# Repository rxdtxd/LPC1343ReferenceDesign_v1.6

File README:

This is a version of microBuilder.eu LPC1343 Reference Board [1],
slightly modified:

- the ocillator footprint is replaced with a HC49/S, these crystals
  are available locally and cheaper;
- spacings are slightly increased (manufacturer requirements);
- silkscreen is now retarded.

[1]: http://www.microbuilder.eu/Projects/LPC1343ReferenceDesign.aspx

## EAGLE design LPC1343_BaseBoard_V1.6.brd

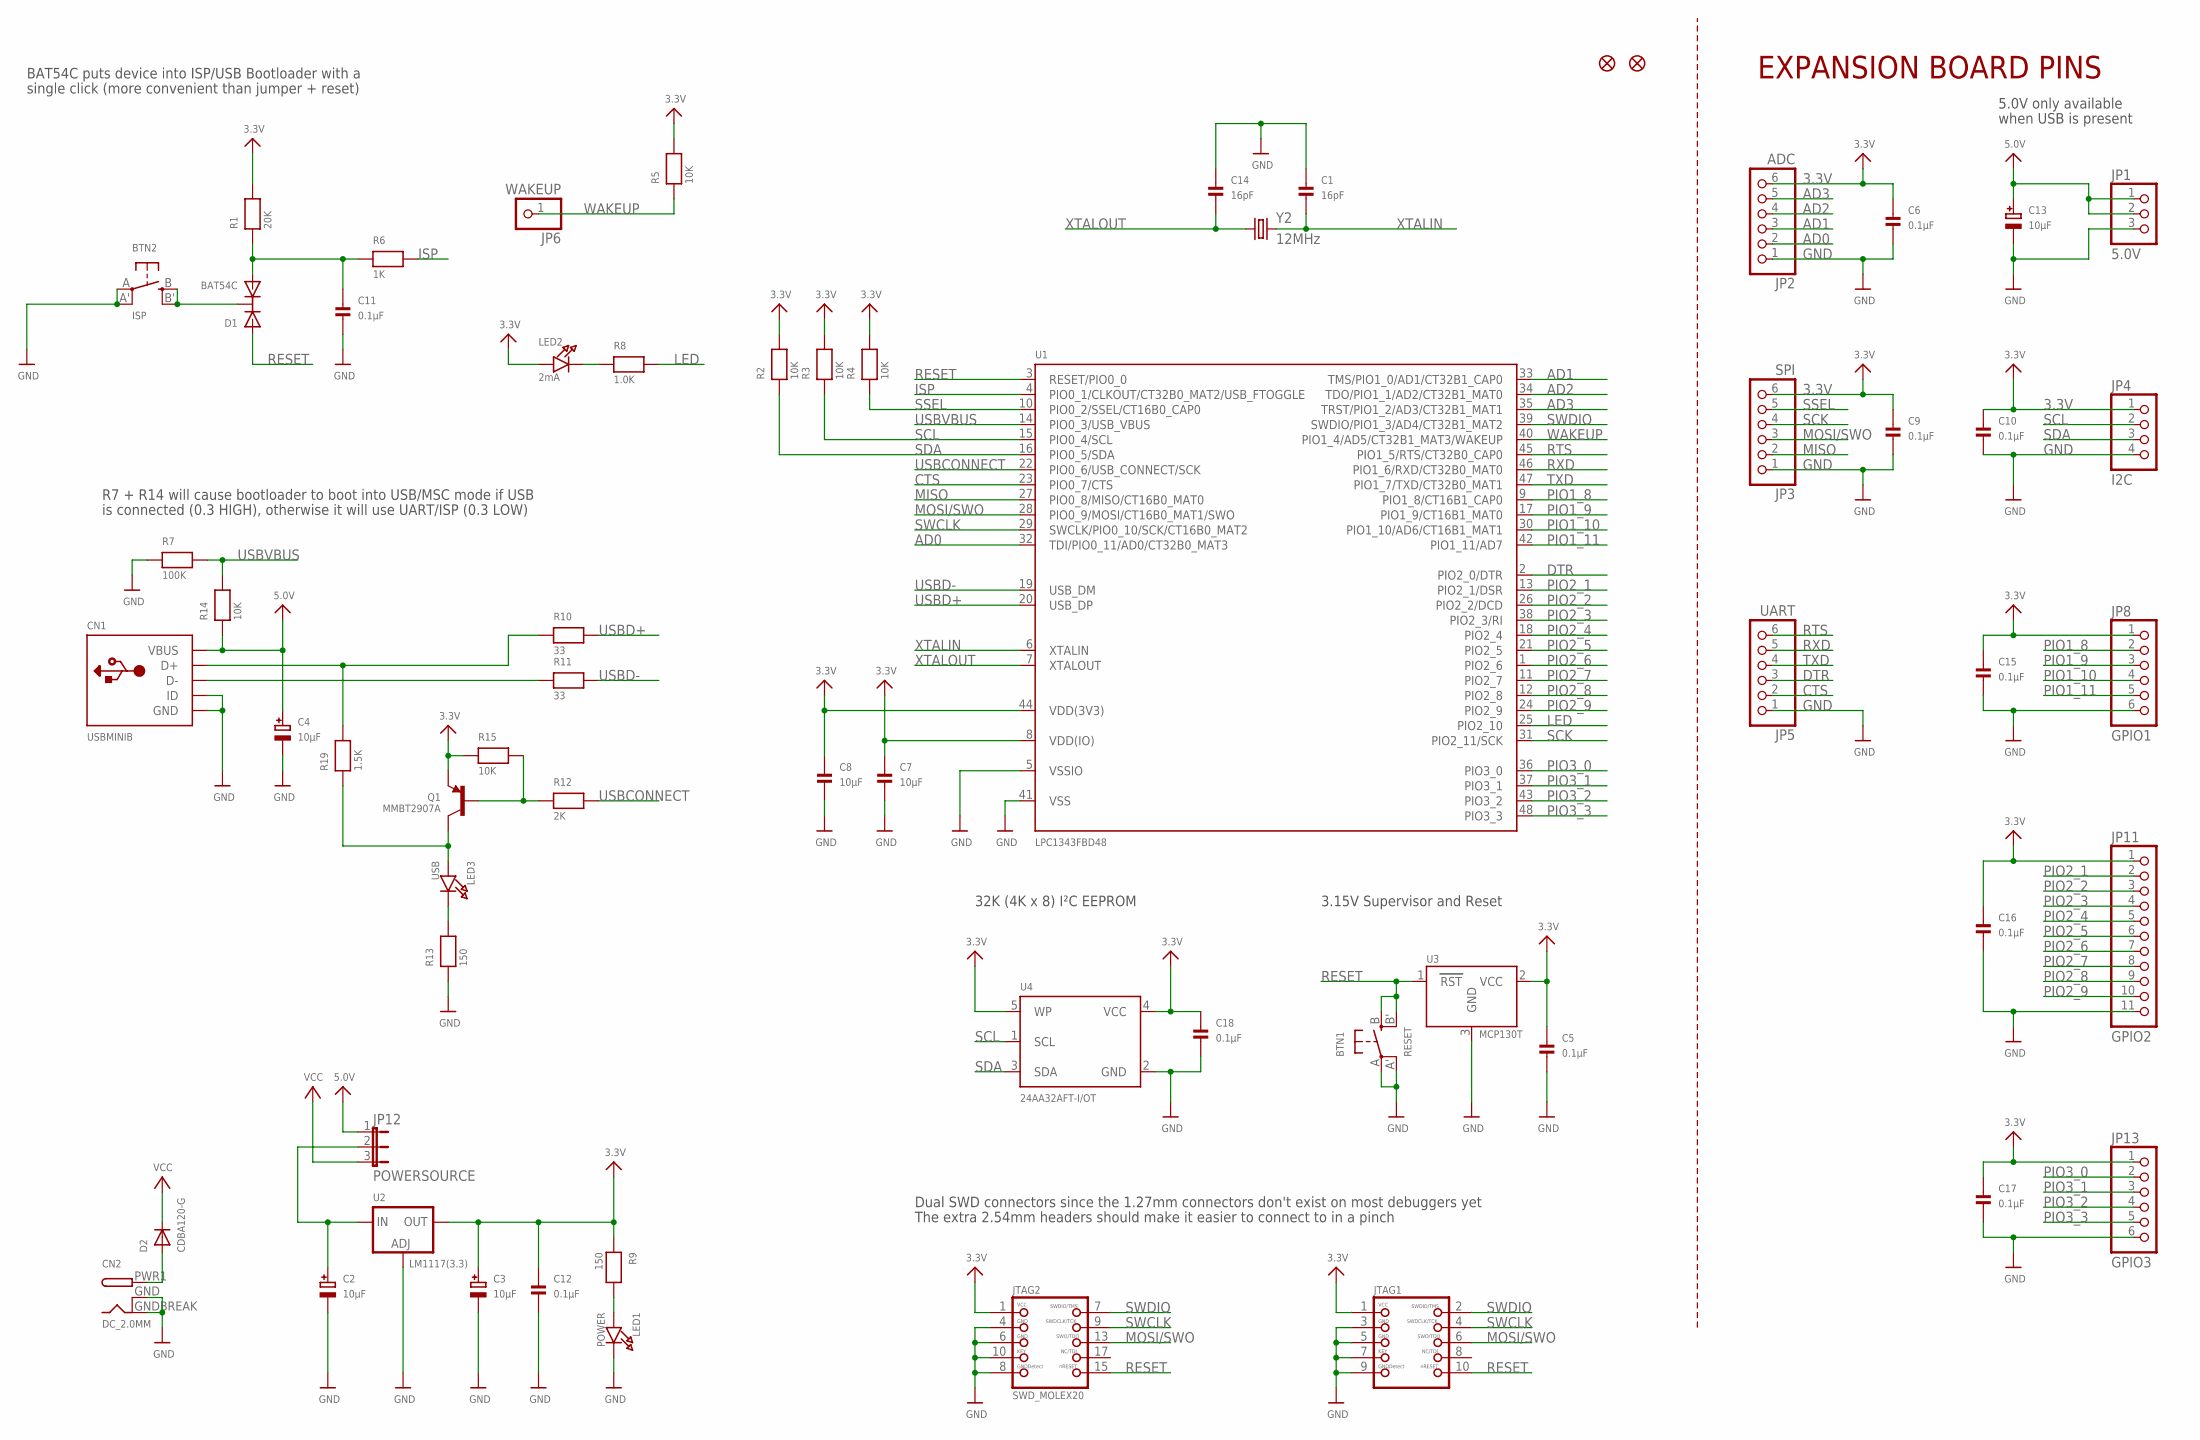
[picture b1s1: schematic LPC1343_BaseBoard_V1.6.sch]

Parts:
BTN1: RESET; EVQ-Q2
BTN2: ISP; EVQ-Q2
C1, C14: 16pF; 0603
C2, C3, C4, C13: 10µF; EIA3216-18/A-R
C5, C6, C9, C10, C11, C12, C15, C16, C17, C18: 0.1µF; 0603
C7, C8: 10µF; 0805
CN1: USBMINIB; USB-MINIB
CN2: DC_2.0MM; DCJACK_2MM_SMT
D1: BAT54C; SOT23-R
D2: CDBA120-G; SMADIODE
JP1: 5.0V; 1X03_ROUND
JP2: ADC; 1X06_ROUND
JP3: SPI; 1X06_ROUND
JP4: I2C; 1X04_ROUND
JP5: UART; 1X06_ROUND
JP6: WAKEUP; 1X01_ROUND
JP7, JP9: FIDUCIAL1X2.5; FIDUCIAL-1X2.5
JP8: GPIO1; 1X06_ROUND
JP11: GPIO2; 1X11_ROUND
JP12: POWERSOURCE; JUMPER3
JP13: GPIO3; 1X06_ROUND
JTAG1: JTAG-CORTEXM3; 2X05_1.27MM_SMT
JTAG2: SWD_MOLEX20; JTAG-ARM
LED1: POWER; CHIPLED_0805
LED2: 2mA; CHIPLED_0805
LED3: USB; CHIPLED_0805
Q1: MMBT2907A; SOT23-R
R1: 20K; 0603
R2, R3, R4, R5, R14, R15: 10K; 0603
R6: 1K; 0603
R7: 100K; 0603
R8: 1.0K; 0603
R9, R13: 150; 0603
R10, R11: 33; 0603
R12: 2K; 0603
R19: 1.5K; 0603
U1: LPC1343FBD48; LQFP48
U2: LM1117(3.3); SOT223-R
U3: MCP130T; SOT23-R
U4: 24AA32AFT-I/OT; SOT23-5
Y2: 12MHz; HC49/S

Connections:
3.3V: C3.+, C5.1, C6.1, C7.1, C8.1, C9.1, C10.1, C12.1, C15.1, C16.1, C17.1, C18.1, JP2.6, JP3.6, JP4.1, JP8.1, JP11.1, JP13.1, JTAG1.1, JTAG2.1, LED2.A, Q1.2 (E), R1.2, R2.2, R3.2, R4.2, R5.2, R9.1, R15.1, U1.8 (VDD(IO)), U1.44 (VDD(3V3)), U2.2 (OUT), U3.2 (VCC), U4.4 (VCC), U4.5 (WP)
5.0V: C4.+, C13.+, CN1.VBUS, JP1.1, JP1.2, JP12.1, R14.1
AD0: JP2.2, U1.32 (TDI/PIO0_11/AD0/CT32B0_MAT3)
AD1: JP2.3, U1.33 (TMS/PIO1_0/AD1/CT32B1_CAP0)
AD2: JP2.4, U1.34 (TDO/PIO1_1/AD2/CT32B1_MAT0)
AD3: JP2.5, U1.35 (TRST/PIO1_2/AD3/CT32B1_MAT1)
CTS: JP5.2, U1.23 (PIO0_7/CTS)
DTR: JP5.3, U1.2 (PIO2_0/DTR)
GND: BTN1.A, BTN1.A' (P1), BTN2.A, BTN2.A' (P1), C1.1, C2.-, C3.-, C4.-, C5.2, C6.2, C7.2, C8.2, C9.2, C10.2, C11.2, C12.2, C13.-, C14.1, C15.2, C16.2, C17.2, C18.2, CN1.GND, CN1.ID, CN2.GND (GNDBREAK), CN2.GNDBREAK (GND), JP1.3, JP2.1, JP3.1, JP4.4, JP5.1, JP8.6, JP11.11, JP13.6, JTAG1.3, JTAG1.5, JTAG1.7, JTAG1.9, JTAG2.4 (3), JTAG2.6 (5), JTAG2.8 (9), JTAG2.10 (7), LED1.C, R7.1, R13.1, U1.5 (VSSIO), U1.41 (VSS), U2.1 (ADJ), U3.3 (GND), U4.2 (GND)
ISP: R6.2, U1.4 (PIO0_1/CLKOUT/CT32B0_MAT2/USB_FTOGGLE)
LED: R8.2, U1.25 (PIO2_10)
MISO: JP3.2, U1.27 (PIO0_8/MISO/CT16B0_MAT0)
MOSI/SWO: JP3.3, JTAG1.6, JTAG2.13 (6), U1.28 (PIO0_9/MOSI/CT16B0_MAT1/SWO)
unnamed: LED2.C, R8.1
unnamed: C2.+, JP12.2, U2.3 (IN)
unnamed: CN2.PWR1 (PWR), D2.A
unnamed: BTN2.B (S), BTN2.B' (S1), D1.3 (C)
unnamed: CN1.D+, R10.1, R19.2
unnamed: Q1.1 (B), R12.1, R15.2
unnamed: C11.1, D1.2 (A2), R1.1, R6.1
unnamed: LED1.A, R9.2
unnamed: LED3.C, R13.2
unnamed: CN1.D-, R11.1
unnamed: LED3.A, Q1.3 (C), R19.1
PIO1_8: JP8.2, U1.9 (PIO1_8/CT16B1_CAP0)
PIO1_9: JP8.3, U1.17 (PIO1_9/CT16B1_MAT0)
PIO1_10: JP8.4, U1.30 (PIO1_10/AD6/CT16B1_MAT1)
PIO1_11: JP8.5, U1.42 (PIO1_11/AD7)
PIO2_1: JP11.2, U1.13 (PIO2_1/DSR)
PIO2_2: JP11.3, U1.26 (PIO2_2/DCD)
PIO2_3: JP11.4, U1.38 (PIO2_3/RI)
PIO2_4: JP11.5, U1.18 (PIO2_4)
PIO2_5: JP11.6, U1.21 (PIO2_5)
PIO2_6: JP11.7, U1.1 (PIO2_6)
PIO2_7: JP11.8, U1.11 (PIO2_7)
PIO2_8: JP11.9, U1.12 (PIO2_8)
PIO2_9: JP11.10, U1.24 (PIO2_9)
PIO3_0: JP13.2, U1.36 (PIO3_0)
PIO3_1: JP13.3, U1.37 (PIO3_1)
PIO3_2: JP13.4, U1.43 (PIO3_2)
PIO3_3: JP13.5, U1.48 (PIO3_3)
RESET: BTN1.B (S), BTN1.B' (S1), D1.1 (A1), JTAG1.10, JTAG2.15 (10), U1.3 (RESET/PIO0_0), U3.1 (RST)
RTS: JP5.6, U1.45 (PIO1_5/RTS/CT32B0_CAP0)
RXD: JP5.5, U1.46 (PIO1_6/RXD/CT32B0_MAT0)
SCK: JP3.4, U1.31 (PIO2_11/SCK)
SCL: JP4.2, R3.1, U1.15 (PIO0_4/SCL), U4.1 (SCL)
SDA: JP4.3, R2.1, U1.16 (PIO0_5/SDA), U4.3 (SDA)
SSEL: JP3.5, R4.1, U1.10 (PIO0_2/SSEL/CT16B0_CAP0)
SWCLK: JTAG1.4, JTAG2.9 (4), U1.29 (SWCLK/PIO0_10/SCK/CT16B0_MAT2)
SWDIO: JTAG1.2, JTAG2.7 (2), U1.39 (SWDIO/PIO1_3/AD4/CT32B1_MAT2)
TXD: JP5.4, U1.47 (PIO1_7/TXD/CT32B0_MAT1)
USBCONNECT: R12.2, U1.22 (PIO0_6/USB_CONNECT/SCK)
USBD+: R10.2, U1.20 (USB_DP)
USBD-: R11.2, U1.19 (USB_DM)
USBVBUS: R7.2, R14.2, U1.14 (PIO0_3/USB_VBUS)
VCC: D2.C, JP12.3
WAKEUP: JP6.1, R5.1, U1.40 (PIO1_4/AD5/CT32B1_MAT3/WAKEUP)
XTALIN: C1.2, U1.6 (XTALIN), Y2.2
XTALOUT: C14.2, U1.7 (XTALOUT), Y2.1

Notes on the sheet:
Dual SWD connectors since the 1.27mm connectors don't exist on most debuggers yet
The extra 2.54mm headers should make it easier to connect to in a pinch
3.15V Supervisor and Reset
5.0V only available
when USB is present
EXPANSION BOARD PINS
R7 + R14 will cause bootloader to boot into USB/MSC mode if USB
is connected (0.3 HIGH), otherwise it will use UART/ISP (0.3 LOW)
BAT54C puts device into ISP/USB Bootloader with a
single click (more convenient than jumper + reset)
32K (4K x 8) I²C EEPROM

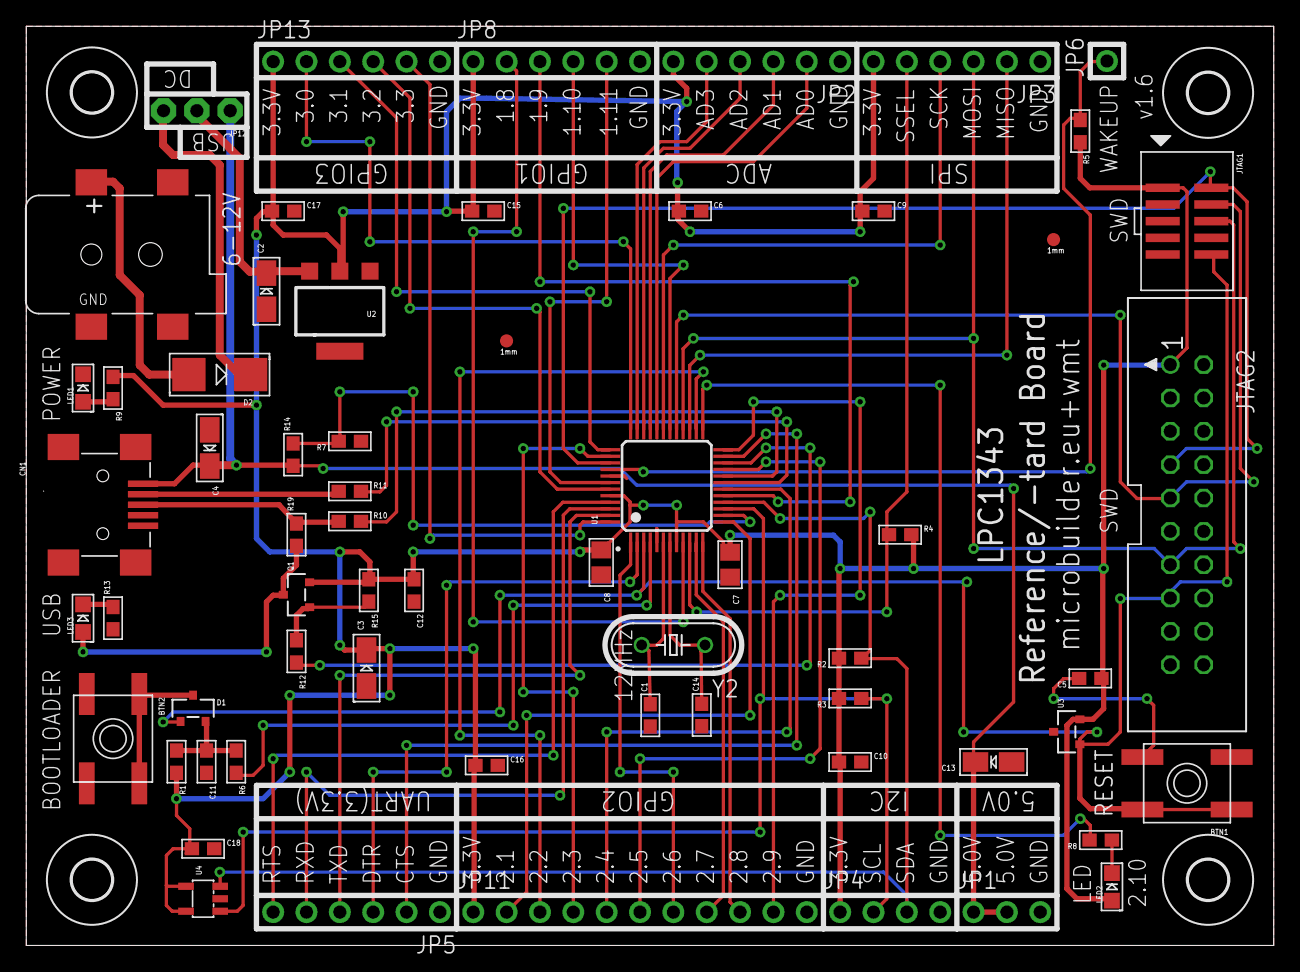
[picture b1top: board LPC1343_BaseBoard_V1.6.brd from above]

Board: 2 copper layers, 95.0 x 70.0 mm, 67 parts (0 on the bottom side), 59 nets.

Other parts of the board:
U$52, U$54, U$55, U$56: MOUNTINGHOLE_3.0

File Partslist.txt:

Partlist

Exported from LPC1343_BaseBoard_V1.6.brd at 1/17/12 9:31 PM

EAGLE Version 6.0.0 Copyright (c) 1988-2011 CadSoft

Assembly variant: 

Part     Value          Package         Library      Position (inch)       Orientation

BTN1     RESET          EVQ-Q2          microbuilder (3.48015748 0.48625984) R180
BTN2     ISP            EVQ-Q2          microbuilder (0.26015748 0.62)     R270
C1       16pF           0603            microbuilder (1.87094488 0.68984252) R90
C2       10µF           EIA3216-18/A-R  microbuilder (0.72015748 1.9615748) R90
C3       10µF           EIA3216-18/A-R  microbuilder (1.02015748 0.8315748) R90
C4       10µF           EIA3216-18/A-R  microbuilder (0.55015748 1.4915748) R270
C5       0.1µF          0603            microbuilder (3.19015748 0.80062992) R180
C6       0.1µF          0603            microbuilder (1.99015748 2.2015748) R0
C7       10µF           0805            microbuilder (2.11015748 1.1415748) R270
C8       10µF           0805            microbuilder (1.72389764 1.1484252) R270
C9       0.1µF          0603            microbuilder (2.54015748 2.2015748) R0
C10      0.1µF          0603            microbuilder (2.47015748 0.55)     R0
C11      0.1µF          0603            microbuilder (0.54047244 0.55094488) R270
C12      0.1µF          0603            microbuilder (1.16267717 1.06440945) R270
C13      10µF           EIA3216-18/A-R  microbuilder (2.90015748 0.55)     R180
C14      16pF           0603            microbuilder (2.02515748 0.69094488) R90
C15      0.1µF          0603            microbuilder (1.37015748 2.2015748) R0
C16      0.1µF          0603            microbuilder (1.38015748 0.54)     R0
C17      0.1µF          0603            microbuilder (0.77015748 2.2015748) R0
C18      0.1µF          0603            microbuilder (0.53015748 0.29)     R0
CN1      USBMINIB       USB-MINIB       microbuilder (0.19015748 1.32125984) R270
CN2      DC_2.0MM       DCJACK_2MM_SMT  microbuilder (0.19515748 2.0715748) R0
D1       BAT54C         SOT23-R         microbuilder (0.50015748 0.71094488) R0
D2       CDBA120-G      SMADIODE        microbuilder (0.58015748 1.7115748) R180
JP1      5.0V           1X03_ROUND      microbuilder (2.94015748 0.1)      R0
JP2      ADC            1X06_ROUND      microbuilder (2.19015748 2.65)     R180
JP3      SPI            1X06_ROUND      microbuilder (2.79015748 2.65)     R180
JP4      I2C            1X04_ROUND      microbuilder (2.59015748 0.1)      R0
JP5      UART           1X06_ROUND      microbuilder (0.99015748 0.1)      R180
JP6      WAKEUP         1X01_ROUND      microbuilder (3.24015748 2.6515748) R90
JP7      FIDUCIAL1X2.5  FIDUCIAL-1X2.5  microbuilder (3.08 2.11629921)     R0
JP8      GPIO1          1X06_ROUND      microbuilder (1.59015748 2.65)     R0
JP9      FIDUCIAL1X2.5  FIDUCIAL-1X2.5  microbuilder (1.44 1.81259843)     R0
JP11     GPIO2          1X11_ROUND      microbuilder (1.84015748 0.1)      R0
JP12     POWERSOURCE    JUMPER3         microbuilder (0.51149606 2.50275591) R180
JP13     GPIO3          1X06_ROUND      microbuilder (0.99015748 2.65)     R0
JTAG1                   2X05_1.27MM_SMT microbuilder (3.48015748 2.1715748) R270
JTAG2    SWD_MOLEX20    JTAG-ARM        microbuilder (3.48015748 1.2915748) R270
LED1     POWER          CHIPLED_0805    microbuilder (0.17015748 1.67125984) R0
LED2     2mA            CHIPLED_0805    microbuilder (3.25515748 0.17562992) R0
LED3     USB            CHIPLED_0805    microbuilder (0.17015748 0.98125984) R0
Q1       MMBT2907A      SOT23-R         microbuilder (0.81015748 1.0515748) R90
R1       20K            0603            microbuilder (0.45047244 0.55094488) R270
R2       10K            0603            microbuilder (2.47015748 0.86125984) R180
R3       10K            0603            microbuilder (2.47015748 0.74062992) R180
R4       10K            0603            microbuilder (2.62015748 1.2315748) R0
R5       10K            0603            microbuilder (3.16015748 2.4415748) R270
R6       1K             0603            microbuilder (0.62937008 0.55094488) R270
R7       100K           0603            microbuilder (0.97015748 1.5115748) R180
R8       1.0K           0603            microbuilder (3.22141732 0.31594488) R180
R9       150            0603            microbuilder (0.26015748 1.67125984) R270
R10      33             0603            microbuilder (0.97015748 1.2715748) R0
R11      33             0603            microbuilder (0.97015748 1.3615748) R0
R12      2K             0603            microbuilder (0.81015748 0.8815748) R270
R13      150            0603            microbuilder (0.26015748 0.98125984) R90
R14      10K            0603            microbuilder (0.80015748 1.4715748) R90
R15      10K            0603            microbuilder (1.02708661 1.06440945) R270
R19      1.5K           0603            microbuilder (0.81015748 1.2315748) R90
U1       LPC1343FBD48   LQFP48          microbuilder (1.92015748 1.37795276) R90
U2       LM1117(3.3)    SOT223-R        microbuilder (0.94015748 1.9015748) R180
U3       MCP130T        SOT23-R         microbuilder (3.11952756 0.64062992) R90
U4       24AA32AFT-I/OT SOT23-5         microbuilder (0.53015748 0.14)     R90
Y2       12MHz          HC49/S          crystal      (1.94015748 0.90094488) R180

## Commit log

2012-01-17 everything in one commit
2012-01-17 oops, get back proper attribution
2012-01-17 add minimal readme
2012-01-17 readme fixed
